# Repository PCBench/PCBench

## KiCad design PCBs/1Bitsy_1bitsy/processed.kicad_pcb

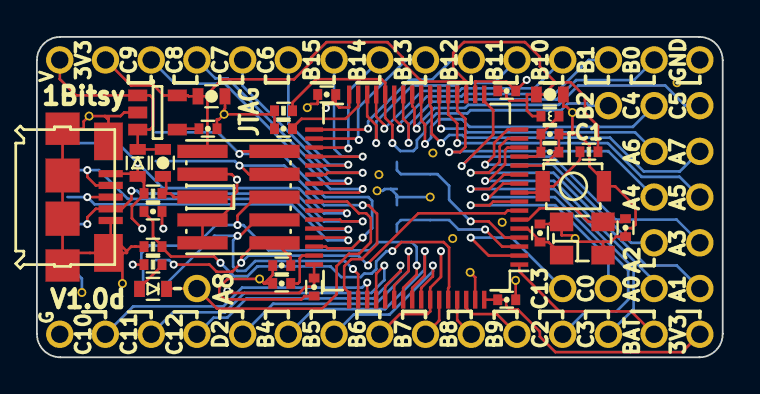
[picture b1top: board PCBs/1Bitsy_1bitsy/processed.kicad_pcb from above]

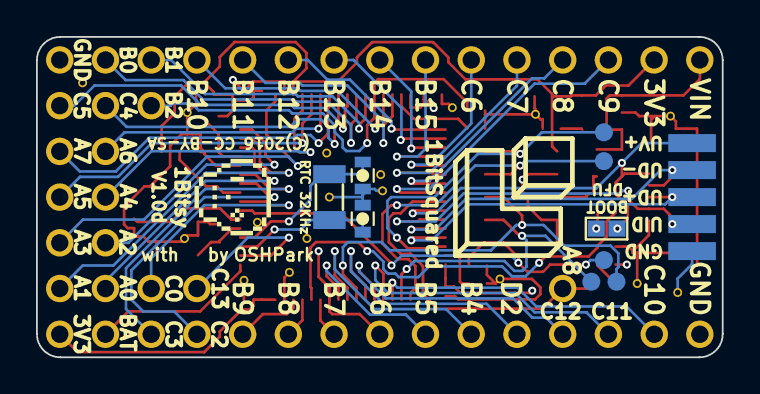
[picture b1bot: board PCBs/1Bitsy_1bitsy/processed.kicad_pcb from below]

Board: 4 copper layers, 38.1 x 17.8 mm, 88 parts (14 on the bottom side), 63 nets.

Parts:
C1, C5, C13: 4u7; C_0603
C2, C15: 1u; C_0402
C3: 470p; C_0402
C4, C10, C11, C12, C14, C18: 100n; C_0402
C6, C7: 10p; C_0603
C8, C9: 10p; C_0402
C16, C17: 2u2; C_0402
D1: >100mA; D_0603
J1: BOOT; J_0603
L1: 600 Ferrite; L_0402
LED1: ORA; D_0603
P1, P2, P3, P4, P5, P6, P7, P8, P9, P10, P11, P12, P13, P14, P15, P16, P17, P18, P19, P20, P21, P22, P23, P25, P26, P27, P28, P29, P30, P31, P32, P33, P34, P35, P36, P37, P38, P39, P40, P41, P42, P53, P54, P55: CONN_01X01; Pin_Header_Straight_Round_1x01
P24: USB_OTG; Connector_USB_Micro_B_SMD
P43, P44, P45, P46, P47: TP; POGO_PAD_SMD_R_1x1
P48, P49, P50, P51, P52: CONN_01X01; PAD_SMD_1x2.65
R1, R2, R3, R5: 10k; R_0402
R4: 300; R_0402
SW1: TACT; Tact_Switch_Top_B3U-1000P
U1: VREG_3V3; SOT-23-5
U2: STM32F415RGT; LQFP-64_10x10mm_Pitch0.5mm
X1: 32.768kHz; ABS07
X2: 25MHz; ABM8
X3: JTAG-10; FTSH-105-XX-X-DV

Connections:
+3V3: C5.1, C10.1, C11.1, C12.1, C13.1, C14.1, L1.1, P42.1, P54.1, R4.1, R5.1, U1.5, U2.19, U2.32, U2.48, U2.64, X3.1
/BOOT0: C15.2, R3.1, U2.60
/BUTTON: R5.2, SW1.2, U2.9
/JTAG_RST: C18.1, P47.1, U2.7, X3.10
/JTAG_TCK: P44.1, U2.49, X3.4
/JTAG_TDI: P46.1, U2.50, X3.8
/JTAG_TDO: P45.1, U2.55, X3.6
/JTAG_TMS: P43.1, U2.46, X3.2
/OSC32_IN: C6.2, U2.3, X1.2
/OSC32_OUT: C7.2, U2.4, X1.1
/OSC_IN: C8.2, U2.5, X2.1
/OSC_OUT: C9.2, U2.6, X2.2
/PA0: P1.1, U2.14
/PA1: P2.1, U2.15
/PA2: P3.1, U2.16
/PA3: P4.1, U2.17
/PA4: P5.1, U2.20
/PA5: P6.1, U2.21
/PA6: P7.1, U2.22
/PA7: P8.1, U2.23
/PA8: LED1.C, P9.1, U2.41
/PB0: P25.1, U2.26
/PB1: P26.1, U2.27
/PB2: P27.1, R2.1, U2.28
/PB4: P28.1, U2.56
/PB5: P29.1, U2.57
/PB6: P30.1, U2.58
/PB7: P31.1, U2.59
/PB8: P32.1, U2.61
/PB9: P33.1, U2.62
/PB10: P34.1, U2.29
/PB11: P35.1, U2.30
/PB12: P36.1, U2.33
/PB13: P37.1, U2.34
/PB14: P38.1, U2.35
/PB15: P39.1, U2.36
/PC0: P10.1, U2.8
/PC2: P12.1, U2.10
/PC3: P13.1, U2.11
/PC4: P14.1, U2.24
/PC5: P15.1, U2.25
/PC6: P16.1, U2.37
/PC7: P17.1, U2.38
/PC8: P18.1, U2.39
/PC9: P19.1, U2.40
/PC10: P20.1, U2.51
/PC11: P21.1, U2.52
/PC12: P22.1, U2.53
/PC13: P23.1, U2.2
/PD2: P11.1, U2.54
/USB_D+: P24.3, P50.1, U2.45
/USB_D-: P24.2, P49.1, U2.44
/USB_ID: P24.4, P51.1, U2.43
/USB_VBUS: D1.A, J1.1, P24.1, P48.1, R1.1, U2.42
/VBAT: P53.1, U2.1
/VIN: C1.1, D1.C, P40.1, U1.1, U1.3
GND: C1.2, C2.2, C3.2, C4.2, C5.2, C6.1, C7.1, C8.1, C9.1, C10.2, C11.2, C12.2, C13.2, C14.2, C16.2, C17.2, C18.2, P24.5, P24.GND, P41.1, P52.1, P55.1, R1.2, R2.2, R3.2, SW1.1, U1.2, U2.12, U2.18, U2.63, X2.GND, X3.3, X3.5, X3.7, X3.9
unnamed: C2.1, C4.1, L1.2, U2.13
unnamed: C3.1, U1.4
unnamed: C15.1, J1.2
unnamed: C16.1, U2.47
unnamed: C17.1, U2.31
unnamed: LED1.A, R4.2

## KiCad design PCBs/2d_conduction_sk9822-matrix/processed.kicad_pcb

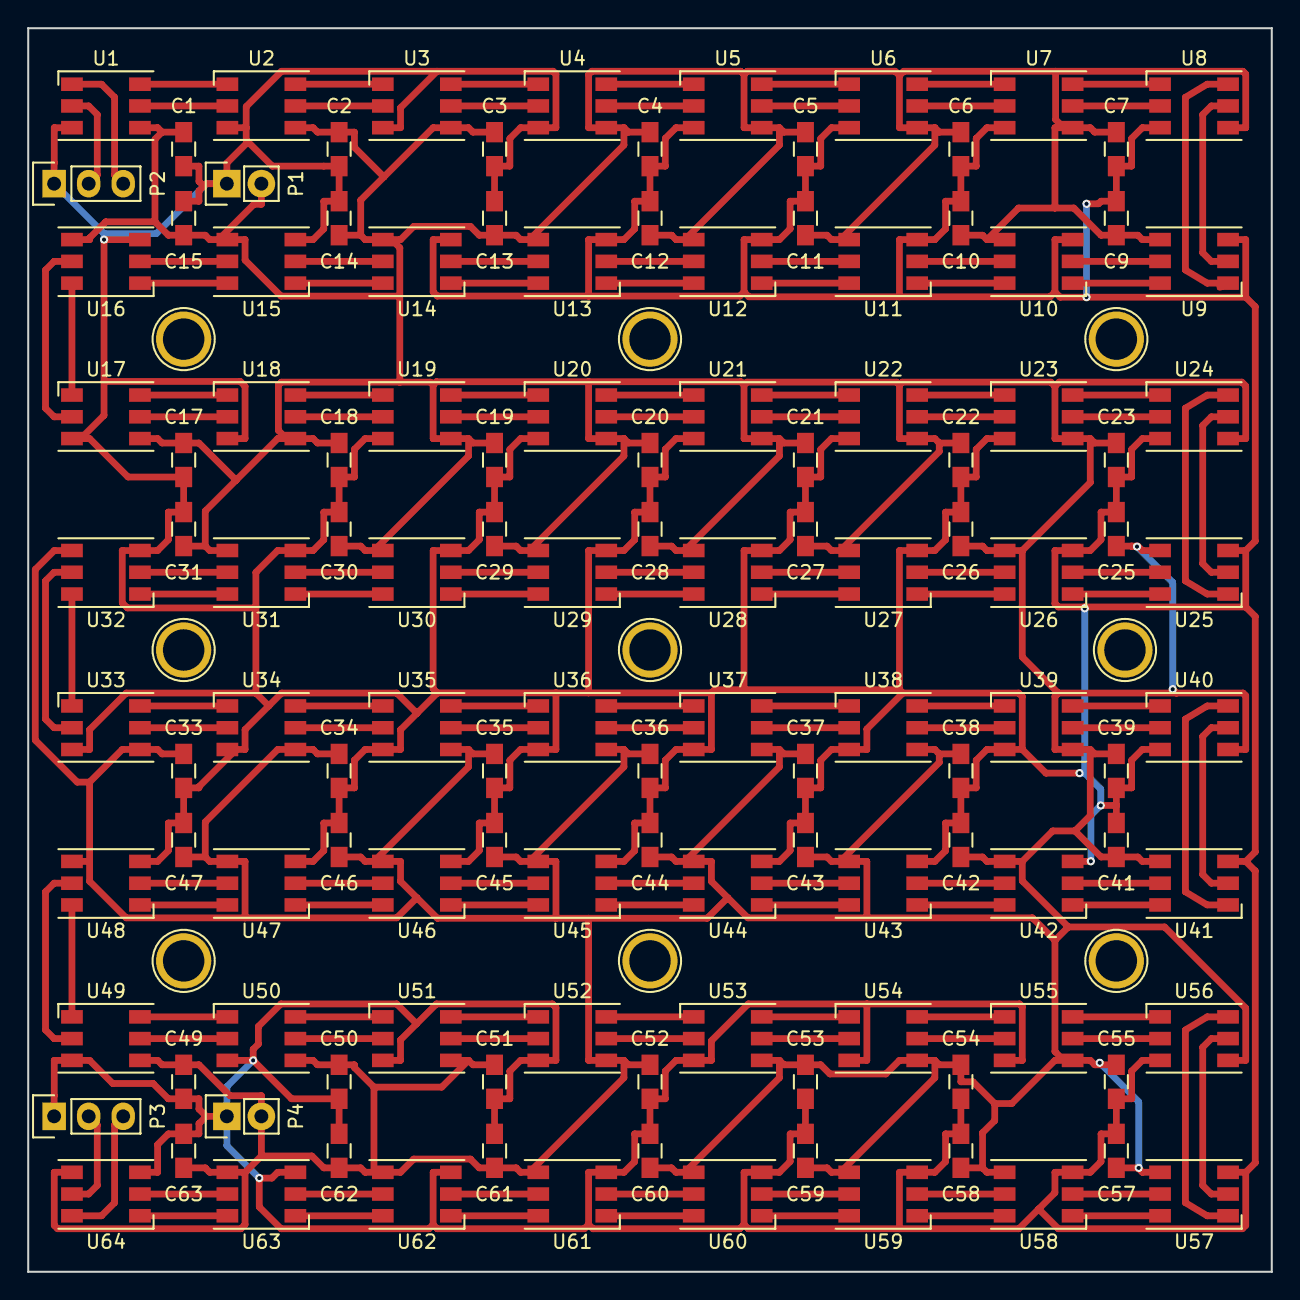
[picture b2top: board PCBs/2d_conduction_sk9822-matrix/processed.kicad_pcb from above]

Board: 2 copper layers, 91.4 x 91.4 mm, 133 parts (0 on the bottom side), 132 nets.

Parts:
C1, C2, C3, C4, C5, C6, C7, C9, C10, C11, C12, C13, C14, C15, C17, C18, C19, C20, C21, C22, C23, C25, C26, C27, C28, C29, C30, C31, C33, C34, C35, C36, C37, C38, C39, C41, C42, C43, C44, C45, C46, C47, C49, C50, C51, C52, C53, C54, C55, C57, C58, C59, C60, C61, C62, C63: 0.1uF; C_0805_HandSoldering
H1, H2, H3, H4, H5, H6, H7, H8, H9: 1pin
P1: PWR IN; Pin_Header_Straight_1x02
P2: DATA IN; Pin_Header_Straight_1x03
P3: DATA OUT; Pin_Header_Straight_1x03
P4: PWR OUT; Pin_Header_Straight_1x02
U1, U2, U3, U4, U5, U6, U7, U8, U9, U10, U11, U12, U13, U14, U15, U16, U17, U18, U19, U20, U21, U22, U23, U24, U25, U26, U27, U28, U29, U30, U31, U32, U33, U34, U35, U36, U37, U38, U39, U40, U41, U42, U43, U44, U45, U46, U47, U48, U49, U50, U51, U52, U53, U54, U55, U56, U57, U58, U59, U60, U61, U62, U63, U64: SK9822; LED_WS2812-PLCC6

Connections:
+5V: C1.2, C2.2, C3.2, C4.2, C5.2, C6.2, C7.2, C9.2, C10.2, C11.2, C12.2, C13.2, C14.2, C15.2, C17.2, C18.2, C19.2, C20.2, C21.2, C22.2, C23.2, C25.2, C26.2, C27.2, C28.2, C29.2, C30.2, C31.2, C33.2, C34.2, C35.2, C36.2, C37.2, C38.2, C39.2, C41.2, C42.2, C43.2, C44.2, C45.2, C46.2, C47.2, C49.2, C50.2, C51.2, C52.2, C53.2, C54.2, C55.2, C57.2, C58.2, C59.2, C60.2, C61.2, C62.2, C63.2, P1.2, P4.2, U1.4, U2.4, U3.4, U4.4, U5.4, U6.4, U7.4, U8.4, U9.4, U10.4, U11.4, U12.4, U13.4, U14.4, U15.4, U16.4, U17.4, U18.4, U19.4, U20.4, U21.4, U22.4, U23.4, U24.4, U25.4, U26.4, U27.4, U28.4, U29.4, U30.4, U31.4, U32.4, U33.4, U34.4, U35.4, U36.4, U37.4, U38.4, U39.4, U40.4, U41.4, U42.4, U43.4, U44.4, U45.4, U46.4, U47.4, U48.4, U49.4, U50.4, U51.4, U52.4, U53.4, U54.4, U55.4, U56.4, U57.4, U58.4, U59.4, U60.4, U61.4, U62.4, U63.4, U64.4
/CKI: P2.2, U1.2
/CKO: P3.2, U64.5
/CKO8: U8.5, U9.2
/CKO16: U16.5, U17.2
/CKO24: U24.5, U25.2
/CKO32: U32.5, U33.2
/CKO40: U40.5, U41.2
/CKO48: U48.5, U49.2
/CKO56: U56.5, U57.2
/SDI: P2.3, U1.1
/SDO: P3.3, U64.6
/SDO8: U8.6, U9.1
/SDO16: U16.6, U17.1
/SDO24: U24.6, U25.1
/SDO32: U32.6, U33.1
/SDO40: U40.6, U41.1
/SDO48: U48.6, U49.1
/SDO56: U56.6, U57.1
GND: C1.1, C2.1, C3.1, C4.1, C5.1, C6.1, C7.1, C9.1, C10.1, C11.1, C12.1, C13.1, C14.1, C15.1, C17.1, C18.1, C19.1, C20.1, C21.1, C22.1, C23.1, C25.1, C26.1, C27.1, C28.1, C29.1, C30.1, C31.1, C33.1, C34.1, C35.1, C36.1, C37.1, C38.1, C39.1, C41.1, C42.1, C43.1, C44.1, C45.1, C46.1, C47.1, C49.1, C50.1, C51.1, C52.1, C53.1, C54.1, C55.1, C57.1, C58.1, C59.1, C60.1, C61.1, C62.1, C63.1, P1.1, P2.1, P3.1, P4.1, U1.3, U2.3, U3.3, U4.3, U5.3, U6.3, U7.3, U8.3, U9.3, U10.3, U11.3, U12.3, U13.3, U14.3, U15.3, U16.3, U17.3, U18.3, U19.3, U20.3, U21.3, U22.3, U23.3, U24.3, U25.3, U26.3, U27.3, U28.3, U29.3, U30.3, U31.3, U32.3, U33.3, U34.3, U35.3, U36.3, U37.3, U38.3, U39.3, U40.3, U41.3, U42.3, U43.3, U44.3, U45.3, U46.3, U47.3, U48.3, U49.3, U50.3, U51.3, U52.3, U53.3, U54.3, U55.3, U56.3, U57.3, U58.3, U59.3, U60.3, U61.3, U62.3, U63.3, U64.3
unnamed: U1.5, U2.2
unnamed: U1.6, U2.1
unnamed: U2.5, U3.2
unnamed: U2.6, U3.1
unnamed: U3.5, U4.2
unnamed: U3.6, U4.1
unnamed: U4.5, U5.2
unnamed: U4.6, U5.1
unnamed: U5.5, U6.2
unnamed: U5.6, U6.1
unnamed: U6.5, U7.2
unnamed: U6.6, U7.1
unnamed: U7.5, U8.2
unnamed: U7.6, U8.1
unnamed: U9.6, U10.1
unnamed: U9.5, U10.2
unnamed: U10.5, U11.2
unnamed: U10.6, U11.1
unnamed: U11.5, U12.2
unnamed: U11.6, U12.1
unnamed: U12.5, U13.2
unnamed: U12.6, U13.1
unnamed: U13.5, U14.2
unnamed: U13.6, U14.1
unnamed: U14.5, U15.2
unnamed: U14.6, U15.1
unnamed: U15.5, U16.2
unnamed: U15.6, U16.1
unnamed: U17.5, U18.2
unnamed: U17.6, U18.1
unnamed: U18.5, U19.2
unnamed: U18.6, U19.1
unnamed: U19.5, U20.2
unnamed: U19.6, U20.1
unnamed: U20.5, U21.2
unnamed: U20.6, U21.1
unnamed: U21.5, U22.2
unnamed: U21.6, U22.1
unnamed: U22.5, U23.2
unnamed: U22.6, U23.1
unnamed: U23.5, U24.2
unnamed: U23.6, U24.1
unnamed: U25.5, U26.2
unnamed: U25.6, U26.1
unnamed: U26.5, U27.2
unnamed: U26.6, U27.1
unnamed: U27.5, U28.2
unnamed: U27.6, U28.1
unnamed: U28.5, U29.2
unnamed: U28.6, U29.1
unnamed: U29.5, U30.2
unnamed: U29.6, U30.1
unnamed: U30.5, U31.2
unnamed: U30.6, U31.1
unnamed: U31.5, U32.2
unnamed: U31.6, U32.1
unnamed: U33.5, U34.2
unnamed: U33.6, U34.1
unnamed: U34.5, U35.2
unnamed: U34.6, U35.1
unnamed: U35.5, U36.2
unnamed: U35.6, U36.1
unnamed: U36.5, U37.2
unnamed: U36.6, U37.1
unnamed: U37.5, U38.2
unnamed: U37.6, U38.1
unnamed: U38.5, U39.2
unnamed: U38.6, U39.1
unnamed: U39.5, U40.2
unnamed: U39.6, U40.1
unnamed: U41.5, U42.2
unnamed: U41.6, U42.1
unnamed: U42.5, U43.2
unnamed: U42.6, U43.1
unnamed: U43.5, U44.2
unnamed: U43.6, U44.1
unnamed: U44.5, U45.2
unnamed: U44.6, U45.1
unnamed: U45.5, U46.2
unnamed: U45.6, U46.1
unnamed: U46.5, U47.2
unnamed: U46.6, U47.1
unnamed: U47.5, U48.2
unnamed: U47.6, U48.1
unnamed: U49.5, U50.2
unnamed: U49.6, U50.1
unnamed: U50.5, U51.2
unnamed: U50.6, U51.1
unnamed: U51.5, U52.2
unnamed: U51.6, U52.1
unnamed: U52.5, U53.2
unnamed: U52.6, U53.1
unnamed: U53.5, U54.2
unnamed: U53.6, U54.1
unnamed: U54.5, U55.2
unnamed: U54.6, U55.1
unnamed: U55.5, U56.2
unnamed: U55.6, U56.1
unnamed: U57.5, U58.2
unnamed: U57.6, U58.1
unnamed: U58.5, U59.2
unnamed: U58.6, U59.1
unnamed: U59.5, U60.2
unnamed: U59.6, U60.1
unnamed: U60.5, U61.2
unnamed: U60.6, U61.1
unnamed: U61.5, U62.2
unnamed: U61.6, U62.1
unnamed: U62.5, U63.2
unnamed: U62.6, U63.1
unnamed: U63.5, U64.2
unnamed: U63.6, U64.1

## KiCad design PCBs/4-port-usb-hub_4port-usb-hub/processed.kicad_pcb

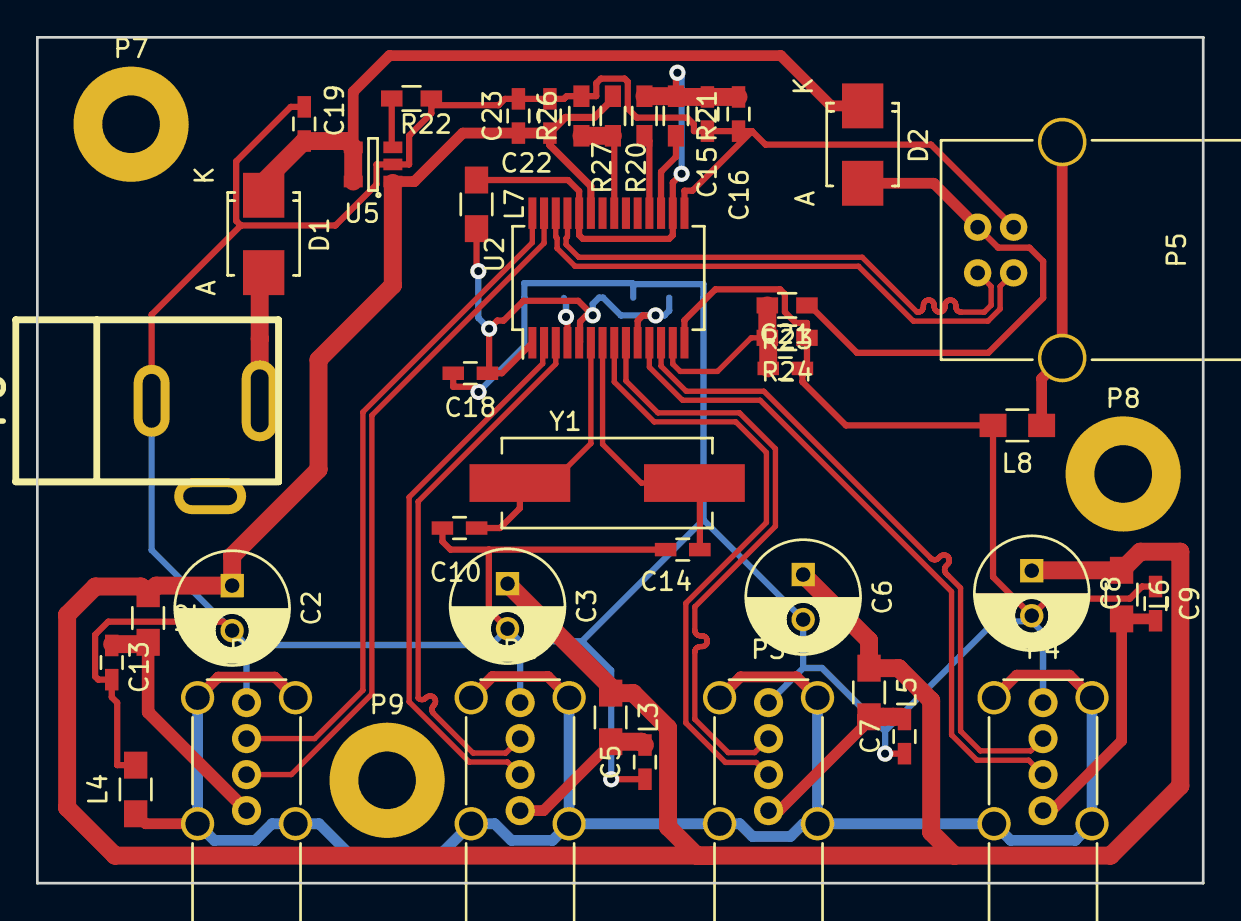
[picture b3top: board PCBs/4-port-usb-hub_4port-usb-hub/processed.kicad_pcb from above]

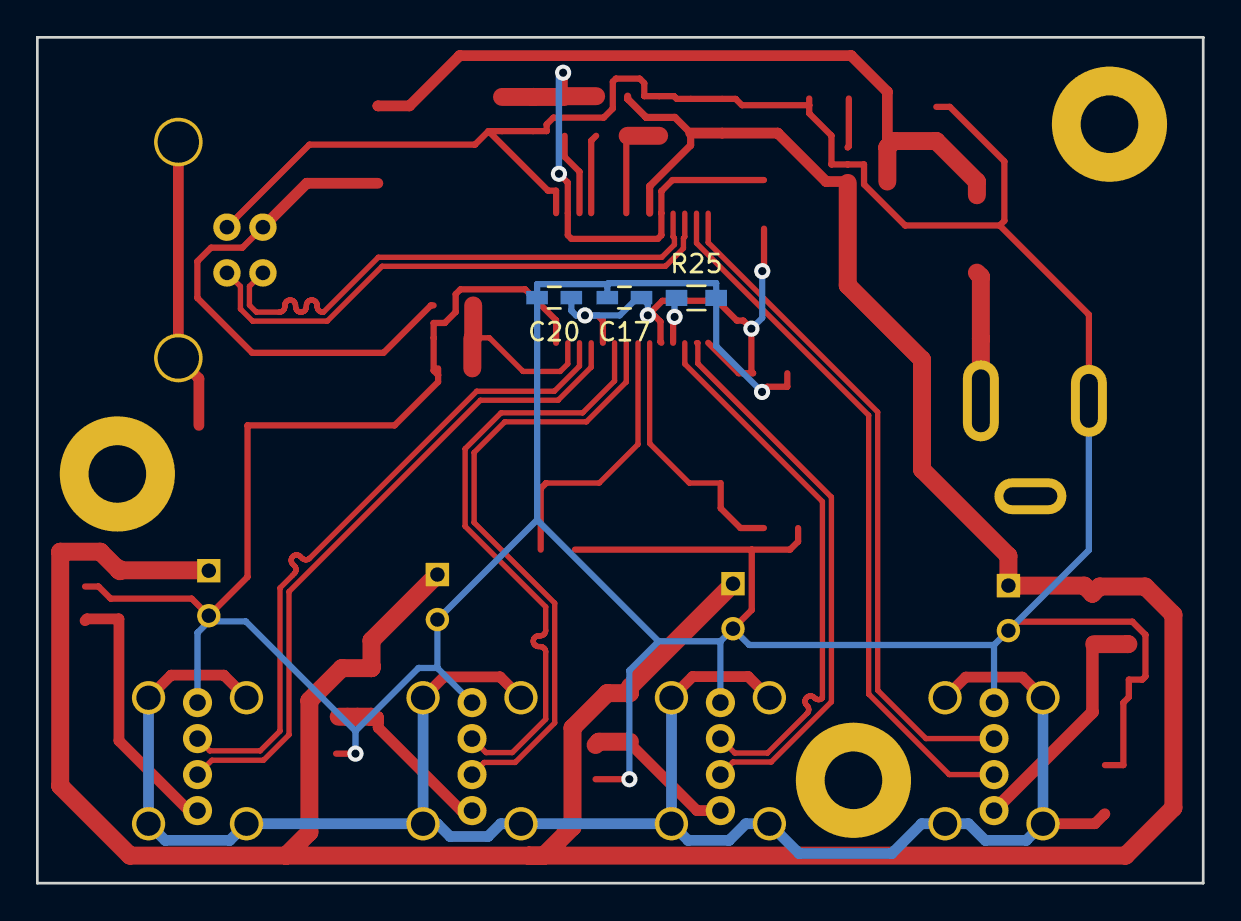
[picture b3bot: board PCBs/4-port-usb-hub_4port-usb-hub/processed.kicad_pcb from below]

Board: 2 copper layers, 64.8 x 47.0 mm, 48 parts (3 on the bottom side), 31 nets.

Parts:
C2, C3, C6, C8: 100uF/16V/LOWESR/105C; C_Radial_D6.3_L11.2_P2.5
C5, C7, C9, C13: 0.1uF; C_0603_HandSoldering
C10, C14: 33pF; C_0603_HandSoldering
C15, C17, C18, C20, C23: 100nF; C_0603_HandSoldering
C16, C19, C22: 10uF/6.3V; C_0603_HandSoldering
C21: 1uF; C_0603_HandSoldering
D1, D2: D; SMB_Standard
L2, L3, L4, L5, L6, L7: 600R/2A; R_0805_HandSoldering
L8: 600R/200mA; R_0805_HandSoldering
P1, P2, P3, P4: USB_A; USB_A_Vertical
P5: USB_B
P6: CONN_01X03; dc_socket
P7, P8, P9: CONN_01X01; MountingHole_3.2mm_M3_Pad
R20, R24: 47k; R_0603_HandSoldering
R21, R23, R26: 10k; R_0603_HandSoldering
R22: 4.7k/1%; R_0603_HandSoldering
R25: 680R/1%; R_0603_HandSoldering
R27: 5.1k; R_0603_HandSoldering
U2: GL850G; SSOP-28_5.3x10.2mm_Pitch0.65mm
U5: SY6280; SOT-23-5
Y1: 12Mhz; Crystal_HC49-SD_SMD

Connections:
/5V: C19.2, D1.1, D2.1, U5.4, U5.5
/5V-DP: C2.1, C3.1, C6.1, C8.1, C22.1, C23.1, L2.1, L3.1, L5.1, L6.1, R27.1, U2.23, U5.1
/5V-IN-USB: D2.2, P5.1, R23.1
/AVDD: C17.1, C18.1, C20.1, L7.2, U2.1, U2.5, U2.10
/V33: C15.1, C16.1, L7.1, R20.1, R21.1, U2.16, U2.24
D0+: P5.3, U2.26
D0-: P5.2, U2.25
D1+: P2.3, U2.28
D1-: P2.2, U2.27
D2+: P1.3, U2.3
D2-: P1.2, U2.2
D3+: P3.3, U2.9
D3-: P3.2, U2.8
D4+: P4.3, U2.12
D4-: P4.2, U2.11
GND: C2.2, C3.2, C5.1, C6.2, C7.1, C8.2, C9.1, C10.2, C13.1, C14.2, C15.2, C16.2, C17.2, C18.2, C19.1, C20.2, C21.2, C22.2, C23.2, L4.2, L8.2, P1.4, P2.4, P3.4, P4.4, P5.4, P6.2, R22.2, R24.1, R25.2, R26.2, U2.14, U2.15, U5.2
unnamed: C5.2, L3.2, P1.1
unnamed: C7.2, L5.2, P3.1
unnamed: C9.2, L6.2, P4.1
unnamed: C10.1, U2.6, Y1.1
unnamed: C13.2, L2.2, P2.1
unnamed: C14.1, U2.7, Y1.2
unnamed: C21.1, R23.2, R24.2, U2.13
unnamed: D1.2, P6.3
unnamed: L4.1, P1.5, P2.5, P3.5, P4.5
unnamed: L8.1, P5.5
unnamed: R20.2, U2.18
unnamed: R21.2, U2.17
unnamed: R22.1, U5.3
unnamed: R25.1, U2.4
unnamed: R26.1, R27.2, U2.21

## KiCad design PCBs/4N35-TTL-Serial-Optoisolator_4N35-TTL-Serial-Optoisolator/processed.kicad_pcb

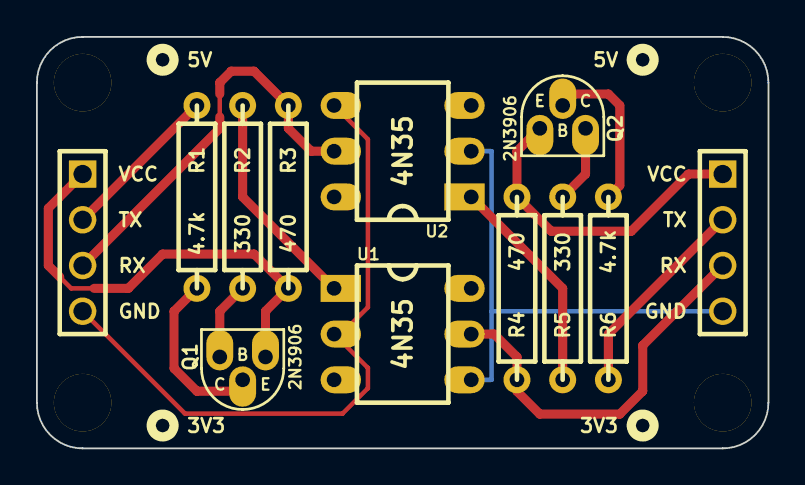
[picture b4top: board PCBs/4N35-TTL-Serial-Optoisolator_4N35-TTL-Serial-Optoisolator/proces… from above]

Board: 2 copper layers, 40.6 x 22.9 mm, 16 parts (0 on the bottom side), 14 nets.

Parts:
H***: Val**; hole_M3_2
H***_2, H***_3, H***_4: Val**; hole_M3_2
P1, P2: CONN_4; PIN_ARRAY_4x1
Q1, Q2: 2N3906; TO-92_Q_EBC_059Bo_PL
R1, R6: 4.7k; R_AXIAL_0W25_059A_PL
R2, R5: 330; R_AXIAL_0W25_059A_PL
R3, R4: 470; R_AXIAL_0W25_059A_PL
U1, U2: 4N35; DIP6_PL

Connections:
GNDA: P1.4, U1.2, U2.4
GNDB: P2.4, U1.4, U2.2
unnamed: Q2.2, R6.2
unnamed: Q2.3, R5.2
unnamed: R5.1, U2.1
unnamed: Q1.3, R2.2
unnamed: Q1.2, R1.2
unnamed: R2.1, U1.1
RXA: P1.3, R3.1, U2.5
RXB: P2.3, R4.1, U1.5
TXA: P1.2, R1.1
TXB: P2.2, R6.1
VCCA: P1.1, Q1.1, R3.2
VCCB: P2.1, Q2.1, R4.2

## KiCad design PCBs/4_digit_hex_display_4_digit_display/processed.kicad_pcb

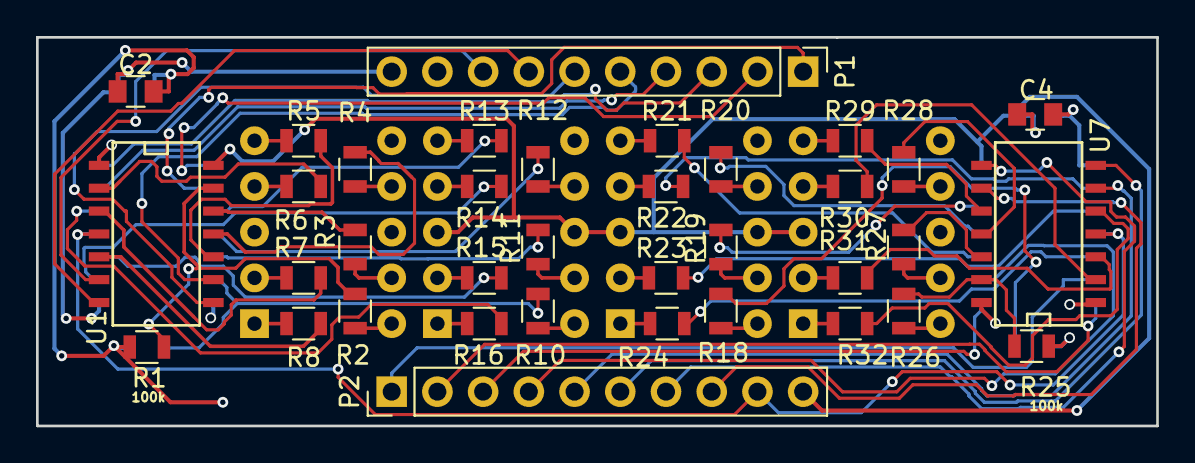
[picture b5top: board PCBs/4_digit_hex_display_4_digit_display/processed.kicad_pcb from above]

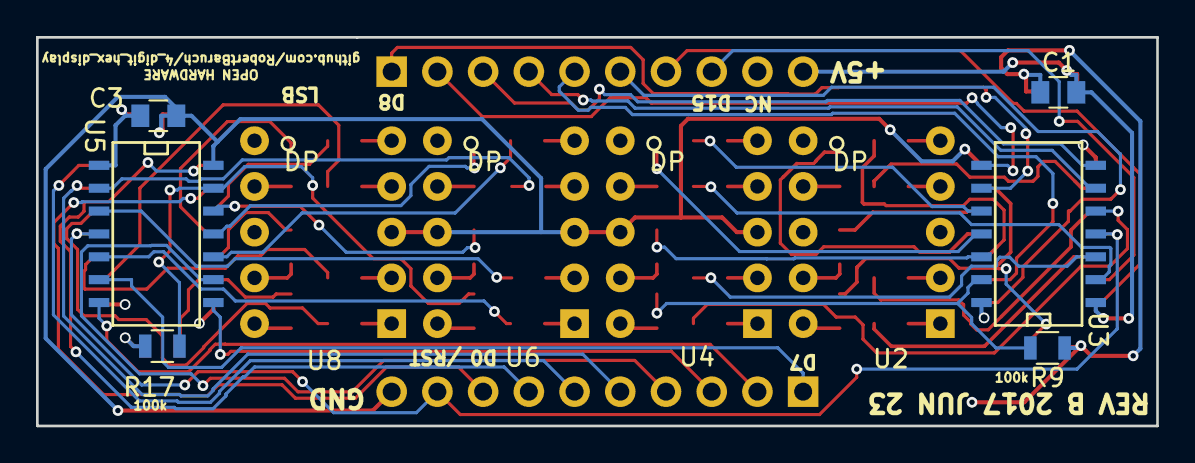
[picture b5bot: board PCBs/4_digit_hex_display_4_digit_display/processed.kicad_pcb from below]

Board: 4 copper layers, 62.2 x 21.6 mm, 46 parts (10 on the bottom side), 75 nets.

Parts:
C1, C2, C3, C4: C; C_0805
P1, P2: CONN_01X10; Pin_Header_Straight_1x10_Pitch2.54mm
R1, R9, R17, R25: 100k; R_0805
R2, R3, R4, R5, R6, R7, R8, R10, R11, R12, R13, R14, R15, R16, R18, R19, R20, R21, R22, R23, R24, R26, R27, R28, R29, R30, R31, R32: 3k3; R_0805
U1, U3, U5, U7: ATTINY84A-SS; SOIC-14_N
U2, U4, U6, U8: TDSR1060; TDSR10

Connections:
+5V: C1.1, C2.1, C3.1, C4.1, P1.10, U1.1, U3.1, U5.1, U7.1
//RST: P2.9, U1.4, U3.4, U5.4, U7.4
/D0: P2.8, U7.9
/D1: P2.7, U7.8
/D2: P2.6, U7.7
/D3: P2.5, U7.6
/D4: P2.4, U5.9
/D5: P2.3, U5.8
/D6: P2.2, U5.7
/D7: P2.1, U5.6
/D8: P1.1, U3.9
/D9: P1.2, U3.8
/D10: P1.3, U3.7
/D11: P1.4, U3.6
/D12: P1.5, U1.9
/D13: P1.6, U1.8
/D14: P1.7, U1.7
/D15: P1.8, U1.6
GNDREF: C1.2, C2.2, C3.2, C4.2, P2.10, R1.1, R9.1, R17.1, R25.1, U1.14, U2.3, U2.8, U3.14, U4.3, U4.8, U5.14, U6.3, U6.8, U7.14, U8.3, U8.8
unnamed: R1.2, R2.2, U1.13
unnamed: R2.1, U2.10
unnamed: R3.1, U2.9
unnamed: R3.2, U1.12
unnamed: R4.1, U2.7
unnamed: R4.2, U1.11
unnamed: R5.1, U2.5
unnamed: R5.2, U1.10
unnamed: R6.1, U2.4
unnamed: R6.2, U1.2
unnamed: R7.1, U2.2
unnamed: R7.2, U1.3
unnamed: R8.1, U2.1
unnamed: R8.2, U1.5
unnamed: R10.1, U4.10
unnamed: R9.2, R10.2, U3.13
unnamed: R11.1, U4.9
unnamed: R11.2, U3.12
unnamed: R12.1, U4.7
unnamed: R12.2, U3.11
unnamed: R13.1, U4.5
unnamed: R13.2, U3.10
unnamed: R14.1, U4.4
unnamed: R14.2, U3.2
unnamed: R15.1, U4.2
unnamed: R15.2, U3.3
unnamed: R16.1, U4.1
unnamed: R16.2, U3.5
unnamed: R17.2, R18.2, U5.13
unnamed: R18.1, U6.10
unnamed: R19.1, U6.9
unnamed: R19.2, U5.12
unnamed: R20.1, U6.7
unnamed: R20.2, U5.11
unnamed: R21.1, U6.5
unnamed: R21.2, U5.10
unnamed: R22.1, U6.4
unnamed: R22.2, U5.2
unnamed: R23.1, U6.2
unnamed: R23.2, U5.3
unnamed: R24.1, U6.1
unnamed: R24.2, U5.5
unnamed: R25.2, R26.2, U7.13
unnamed: R26.1, U8.10
unnamed: R27.1, U8.9
unnamed: R27.2, U7.12
unnamed: R28.1, U8.7
unnamed: R28.2, U7.11
unnamed: R29.1, U8.5
unnamed: R29.2, U7.10
unnamed: R30.1, U8.4
unnamed: R30.2, U7.2
unnamed: R31.1, U8.2
unnamed: R31.2, U7.3
unnamed: R32.1, U8.1
unnamed: R32.2, U7.5

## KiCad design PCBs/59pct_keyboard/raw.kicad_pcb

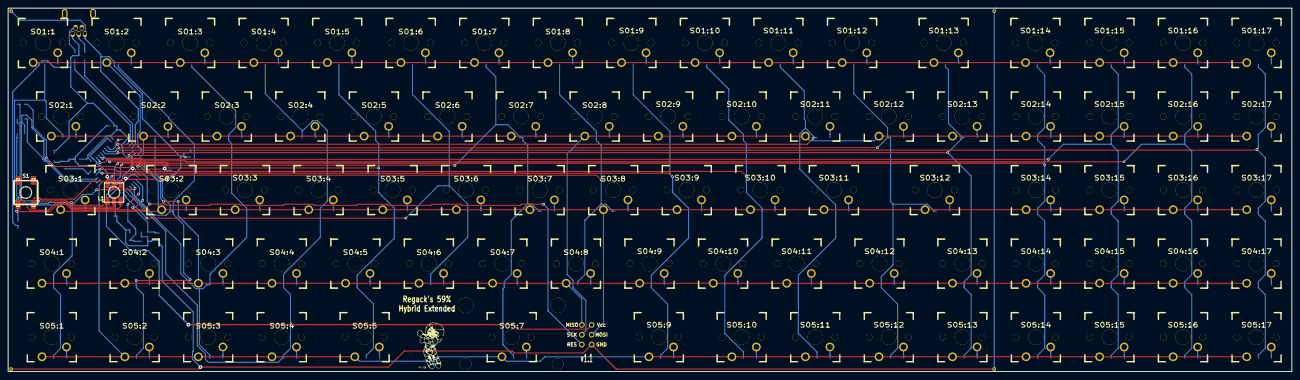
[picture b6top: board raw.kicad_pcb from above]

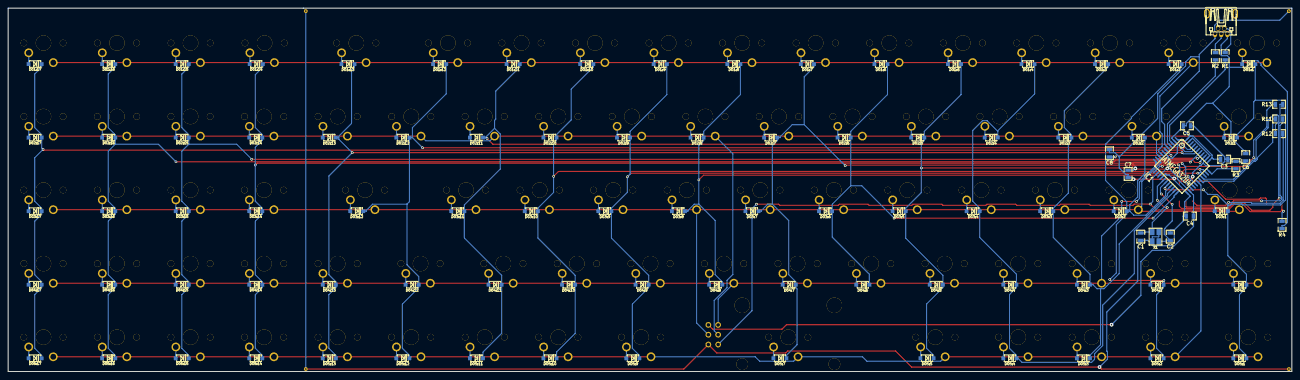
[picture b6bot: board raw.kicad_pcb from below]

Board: 2 copper layers, 332.5 x 94.1 mm, 195 parts (104 on the bottom side), 121 nets.

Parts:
C1, C2: 22pF; SM0805
C3, C4, C5, C6: 0.1uF; SM0805
C7, C8: 1uF; SM0805
D01:1, D01:2, D01:3, D01:4, D01:5, D01:6, D01:7, D01:8, D01:9, D01:10, D01:11, D01:12, D01:13, D01:14, D01:15, D01:16, D01:17, D02:1, D02:2, D02:3, D02:4, D02:5, D02:6, D02:7, D02:8, D02:9, D02:10, D02:11, D02:12, D02:13, D02:14, D02:15, D02:16, D02:17, D03:1, D03:2, D03:3, D03:4, D03:5, D03:6, D03:7, D03:8, D03:9, D03:10, D03:11, D03:12, D03:14, D03:15, D03:16, D03:17, D04:1, D04:2, D04:3, D04:4, D04:5, D04:6, D04:7, D04:8, D04:9, D04:10, D04:11, D04:12, D04:13, D04:14, D04:15, D04:16, D04:17, D05:1, D05:2, D05:3, D05:4, D05:5, D05:7, D05:9, D05:10, D05:11, D05:12, D05:13, D05:14, D05:15, D05:16, D05:17: 1N4148; SOD-123(A-C)
G4: Graphic; Silkscreen_Regack_100x150
IC1: ATMEGA32U4; TQFP44
J1: USB MINI-B; USB_MINI-B_MOLEX_54819-0519
L1: RGB_SMD_LED; RGBLED5050
P1, P2, P3, P4: GND; Pad_Gnd
P5: MISO; Pad
P6: Vcc; Pad
P7: SCK; Pad
P8: MOSI; Pad
P9: RES; Pad
P10: GND; Pad
R1, R2: 22Ω; SM0805
R3, R4: 10kΩ; SM0805
R11, R13: RESISTOR; SM0805
R12: 120; SM0805
S1: ADTSMW69NVTR; ADTSJW65RV
S01:1, S01:2, S01:3, S01:4, S01:5, S01:6, S01:7, S01:8, S01:9, S01:10, S01:11, S01:12, S01:14, S01:15, S01:16, S01:17, S02:2, S02:3, S02:4, S02:5, S02:6, S02:7, S02:8, S02:9, S02:10, S02:11, S02:12, S02:13, S02:14, S02:15, S02:16, S02:17, S03:2, S03:3, S03:4, S03:5, S03:6, S03:7, S03:8, S03:9, S03:10, S03:11, S03:14, S03:15, S03:16, S03:17, S04:2, S04:3, S04:4, S04:5, S04:6, S04:7, S04:8, S04:9, S04:10, S04:11, S04:13, S04:14, S04:15, S04:16, S04:17, S05:2, S05:3, S05:4, S05:10, S05:11, S05:12, S05:13, S05:14, S05:15, S05:16, S05:17: MX1A; CHERRY_PCB_100H_Plated
S01:13, S02:1: MX1A; CHERRY_PCB_150H_Visible
S03:1, S03:12: MX1A; CHERRY_PCB_175H_Visible
S04:1, S04:12, S05:1, S05:5, S05:9: MX1A; CHERRY_PCB_125H_Visible
S05:7: MX1A; CHERRY_PCB_275H_Visible
X1: 7M-16.000MAAJ-T

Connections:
/Matrix/col1: D01:1.C, D02:1.C, D03:1.C, D04:1.C, D05:1.C, IC1.18
/Matrix/col2: D01:2.C, D02:2.C, D03:2.C, D04:2.C, D05:2.C, IC1.19
/Matrix/col3: D01:3.C, D02:3.C, D03:3.C, D04:3.C, D05:3.C, IC1.20
/Matrix/col4: D01:4.C, D02:4.C, D03:4.C, D04:4.C, D05:4.C, IC1.21
/Matrix/col5: D01:5.C, D02:5.C, D03:5.C, D04:5.C, D05:5.C, IC1.25
/Matrix/col6: D01:6.C, D02:6.C, D03:6.C, D04:6.C, IC1.22
/Matrix/col7: D01:7.C, D02:7.C, D03:7.C, D04:7.C, D05:7.C, IC1.26
/Matrix/col8: D01:8.C, D02:8.C, D03:8.C, D04:8.C, IC1.27
/Matrix/col9: D01:9.C, D02:9.C, D03:9.C, D04:9.C, D05:9.C, IC1.31
/Matrix/col10: D01:10.C, D02:10.C, D03:10.C, D04:10.C, D05:10.C, IC1.32
/Matrix/col11: D01:11.C, D02:11.C, D03:11.C, D04:11.C, D05:11.C, IC1.41
/Matrix/col12: D01:12.C, D02:12.C, D03:12.C, D04:12.C, D05:12.C, IC1.40
/Matrix/col13: D01:13.C, D02:13.C, D04:13.C, D05:13.C, IC1.39
/Matrix/col14: D01:14.C, D02:14.C, D03:14.C, D04:14.C, D05:14.C, IC1.38
/Matrix/col15: D01:15.C, D02:15.C, D03:15.C, D04:15.C, D05:15.C, IC1.37
/Matrix/col16: D01:16.C, D02:16.C, D03:16.C, D04:16.C, D05:16.C, IC1.36
/Matrix/col17: D01:17.C, D02:17.C, D03:17.C, D04:17.C, D05:17.C, IC1.1
/Matrix/row1: IC1.8, S01:1.1, S01:2.1, S01:3.1, S01:4.1, S01:5.1, S01:6.1, S01:7.1, S01:8.1, S01:9.1, S01:10.1, S01:11.1, S01:12.1, S01:13.1, S01:14.1, S01:15.1, S01:16.1, S01:17.1
/Matrix/row2: IC1.9, P7.1, S02:1.1, S02:2.1, S02:3.1, S02:4.1, S02:5.1, S02:6.1, S02:7.1, S02:8.1, S02:9.1, S02:10.1, S02:11.1, S02:12.1, S02:13.1, S02:14.1, S02:15.1, S02:16.1, S02:17.1
/Matrix/row3: IC1.10, P8.1, S03:1.1, S03:2.1, S03:3.1, S03:4.1, S03:5.1, S03:6.1, S03:7.1, S03:8.1, S03:9.1, S03:10.1, S03:11.1, S03:12.1, S03:14.1, S03:15.1, S03:16.1, S03:17.1
/Matrix/row4: IC1.11, P5.1, S04:1.1, S04:2.1, S04:3.1, S04:4.1, S04:5.1, S04:6.1, S04:7.1, S04:8.1, S04:9.1, S04:10.1, S04:11.1, S04:12.1, S04:13.1, S04:14.1, S04:15.1, S04:16.1, S04:17.1
/Matrix/row5: IC1.28, S05:1.1, S05:2.1, S05:3.1, S05:4.1, S05:5.1, S05:7.1, S05:9.1, S05:10.1, S05:11.1, S05:12.1, S05:13.1, S05:14.1, S05:15.1, S05:16.1, S05:17.1
/PWM1: IC1.29, R11.2
/PWM2: IC1.30, R12.2
/PWM3: IC1.12, R13.2
/~RES~: IC1.13, P9.1, R4.2, S1.4
GND: C1.2, C2.2, C3.2, C4.2, C5.2, C6.2, C7.2, C8.2, IC1.5, IC1.15, IC1.23, IC1.35, IC1.43, J1.5, L1.4, L1.5, L1.6, P1.1, P2.1, P3.1, P4.1, P10.1, R3.2, S1.2, X1.2, X1.4
unnamed: J1.2, R1.2
unnamed: J1.3, R2.2
unnamed: IC1.4, R2.1
unnamed: IC1.3, R1.1
unnamed: IC1.33, R3.1
unnamed: C8.1, IC1.6
unnamed: L1.1, R12.1
unnamed: C1.1, IC1.16, X1.1
unnamed: C2.1, IC1.17, X1.3
unnamed: L1.3, R13.1
unnamed: L1.2, R11.1
unnamed: D04:1.A, S04:1.2
unnamed: D04:13.A, S04:13.2
unnamed: D05:11.A, S05:11.2
unnamed: D05:12.A, S05:12.2
unnamed: D05:13.A, S05:13.2
unnamed: D05:7.A, S05:7.2
unnamed: D03:1.A, S03:1.2
unnamed: D05:4.A, S05:4.2
unnamed: D05:1.A, S05:1.2
unnamed: D05:2.A, S05:2.2
unnamed: D05:3.A, S05:3.2
unnamed: D05:5.A, S05:5.2
unnamed: D05:9.A, S05:9.2
unnamed: D05:10.A, S05:10.2
unnamed: D03:12.A, S03:12.2
unnamed: D04:9.A, S04:9.2
unnamed: D04:10.A, S04:10.2
unnamed: D04:11.A, S04:11.2
unnamed: D04:12.A, S04:12.2
unnamed: D03:11.A, S03:11.2
unnamed: D02:13.A, S02:13.2
unnamed: D02:12.A, S02:12.2
unnamed: D02:5.A, S02:5.2
unnamed: D03:9.A, S03:9.2
unnamed: D02:9.A, S02:9.2
unnamed: D01:10.A, S01:10.2
unnamed: D01:13.A, S01:13.2
unnamed: D02:10.A, S02:10.2
unnamed: D01:11.A, S01:11.2
unnamed: D02:11.A, S02:11.2
unnamed: D03:10.A, S03:10.2
unnamed: D04:8.A, S04:8.2
unnamed: D01:12.A, S01:12.2
unnamed: D04:5.A, S04:5.2
unnamed: D04:7.A, S04:7.2
unnamed: D05:14.A, S05:14.2
unnamed: D05:15.A, S05:15.2
unnamed: D05:16.A, S05:16.2
unnamed: D05:17.A, S05:17.2
unnamed: D04:15.A, S04:15.2
unnamed: D04:16.A, S04:16.2
unnamed: D04:17.A, S04:17.2
unnamed: D01:16.A, S01:16.2
unnamed: D01:17.A, S01:17.2
unnamed: D02:14.A, S02:14.2
unnamed: D02:15.A, S02:15.2
unnamed: D01:14.A, S01:14.2
unnamed: D01:15.A, S01:15.2
unnamed: D03:15.A, S03:15.2
unnamed: D03:16.A, S03:16.2
unnamed: D03:17.A, S03:17.2
unnamed: D04:14.A, S04:14.2
unnamed: D02:16.A, S02:16.2
unnamed: D02:17.A, S02:17.2
unnamed: D03:14.A, S03:14.2
unnamed: D01:7.A, S01:7.2
unnamed: D01:9.A, S01:9.2
unnamed: D04:4.A, S04:4.2
unnamed: D02:2.A, S02:2.2
unnamed: D02:3.A, S02:3.2
unnamed: D02:4.A, S02:4.2
unnamed: D02:6.A, S02:6.2
unnamed: D02:7.A, S02:7.2
unnamed: D02:1.A, S02:1.2
unnamed: D02:8.A, S02:8.2
unnamed: D01:6.A, S01:6.2
unnamed: D01:1.A, S01:1.2
unnamed: D01:2.A, S01:2.2
unnamed: D01:3.A, S01:3.2
unnamed: D01:4.A, S01:4.2
unnamed: D01:5.A, S01:5.2
unnamed: D01:8.A, S01:8.2
unnamed: D04:2.A, S04:2.2
unnamed: D04:3.A, S04:3.2
unnamed: D04:6.A, S04:6.2
unnamed: D03:2.A, S03:2.2
unnamed: D03:3.A, S03:3.2
unnamed: D03:4.A, S03:4.2
unnamed: D03:5.A, S03:5.2
unnamed: D03:6.A, S03:6.2
unnamed: D03:7.A, S03:7.2
unnamed: D03:8.A, S03:8.2
VCC: C3.1, C4.1, C5.1, C6.1, C7.1, IC1.2, IC1.7, IC1.14, IC1.24, IC1.34, IC1.44, J1.1, P6.1, R4.1

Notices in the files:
PCBs/1Bitsy_1bitsy/processed.kicad_pcb:
(C) 2016 Piotr Esden-Tempski
(C) 2016 1BitSquared LLC
License: CC-BY-SA V4.0
(C)2016 CC-BY-SA
